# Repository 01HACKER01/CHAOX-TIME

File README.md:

# CHAOX-TIME

this is a digital alarm clock 

This is my second hardware project 
I wanted to build it all by myself alone but i dont know how to code so i used AI to make the code 
for now i have used but i will learn code asap and then make it by myself 

## BOM

| Part | Qty | Approx. USD | Link |
| -------------------------------------- | -- | ------------ | -------------------------------------------------------------------------------------------------------------------------------------------------------------- |
| Seeed XIAO ESP32-C3 | 1 | $6 | [Seeed](https://www.seeedstudio.com/Seeed-Studio-XIAO-ESP32C3-Pre-Soldered-p-6331.html) |
| 2.8" ILI9341 240×320 **8-pin SPI TFT** | 1 | $4–8 | [Alibaba – 8-pin version](https://german.alibaba.com/product-detail/2-8-Inch-240x320-SPI-Interface-1600692821834.html) |
| MCP23017-E/SP DIP-28 | 1 | ~$1.69 | [Mouser](https://www.mouser.co.uk/en/ProductDetail/Microchip-Technology/MCP23017-E-SP) |
| MAX98357A I²S amplifier module | 1 | ~$1–6 | [Alibaba MAX98357A](https://www.alibaba.com/product-detail/MAX98357A-Audio-Amplifier-Module-3006-I2S_1601639879756.html) |
| 8Ω 3W speaker | 1 | ~$1–4 | [Alibaba 8Ω 3W speakers](https://electronics.alibaba.com/buyingguides/8-ohm-3w-speaker-buying-guide) |
| 3.3V piezo buzzer | 1 | ~$0.50–1.50 | [Alibaba piezo buzzers](https://www.alibaba.com/trade/search?SearchText=3.3V+piezo+buzzer) |
| MX/Cherry-MX compatible switches | 12 | ~$3–6 | [Alibaba MX switches](https://www.alibaba.com/trade/search?SearchText=MX+mechanical+switches) |
| 1N4148 DO-35 diodes | 12 | ~$0.50–1.50 | [Alibaba 1N4148](https://www.alibaba.com/trade/search?SearchText=1N4148+DO-35) |
| 4.7kΩ ¼W THT resistors | 2 | ~$0.10–0.30 | [Alibaba 4.7k resistors](https://www.alibaba.com/trade/search?SearchText=4.7k+ohm+1%2F4W+resistor) |
| 100nF THT capacitors | 3 | ~$0.20–0.60 | [Alibaba 100nF THT capacitors](https://www.alibaba.com/trade/search?SearchText=100nF+THT+capacitor) |
| 10µF radial electrolytic capacitor | 1 | ~$0.10–0.30 | [Alibaba 10µF capacitors](https://www.alibaba.com/trade/search?SearchText=10uF+radial+electrolytic+capacitor) |
| 1×8 2.54mm header | 1 | ~$0.10–0.30 | [Alibaba 1×8 header](https://www.alibaba.com/trade/search?SearchText=1x8+2.54mm+pin+header) |
| 1×7 2.54mm header | 1 | ~$0.10–0.30 | [Alibaba 1×7 header](https://www.alibaba.com/trade/search?SearchText=1x7+2.54mm+pin+header) |
| 1×2 2.54mm header | 1 | ~$0.05–0.15 | [Alibaba 1×2 header](https://www.alibaba.com/trade/search?SearchText=1x2+2.54mm+pin+header) |
| M3×5×4 heat-set inserts | 8 | ~$1–3 | [Alibaba M3 heat-set inserts](https://www.alibaba.com/trade/search?SearchText=M3+heat+set+inserts+5x4) |
| M3×8 screws | 4 | ~$0.30–1 | [Alibaba M3×8 screws](https://www.alibaba.com/trade/search?SearchText=M3x8+screws) |
| M3×16 screws | 4 | ~$0.40–1 | [Alibaba M3×16 screws](https://www.alibaba.com/trade/search?SearchText=M3x16+screws) |
| USB-A → USB-C cable | 1 | ~$2–4 | [Alibaba USB-C cable](https://www.alibaba.com/trade/search?SearchText=USB+A+to+USB+C+cable) |
| 5V USB power adapter | 1 | ~$3–6 | [Alibaba 5V adapter](https://www.alibaba.com/trade/search?SearchText=5V+USB+power+adapter) |

### 💰 Estimated total

**Parts: About $25–50 USD**

**Estimated shipping: ~$20 USD**

**Total including shipping: About $45–70 USD**, depending heavily on the seller, quantity and shipping.

#Features 

the current verdion has some less features than what i assumed when i started this project cause i forgot i had to code it myself but i dont know how to code so rn it has some less features but i m learning c++ so that i can add all the features i thought of when i started this project 

so now the features it has rn:
- shows the current time 
- it can fetch the time and date from internet using wifi
- it can set only 1 alarm //for now
- it beeps when alarm goes off
- we can stop the alam by 1 button

i have added the hardware in the PCB for future updates 

#Hardware

The main controller is the seeed xiao esp32 c3 board which controlls the whole clock 
itt has 12 switches so that we can change any setting we want 

the pcb contains:

- Seeed XIAO ESP32-C3
- 2.8" ILI9341 SPI TFT
- MCP23017-E/SP GPIO expander
- 12 MX/Cherry-MX compatible switches
- 12 × 1N4148 diodes
- 3.3V piezo buzzer
- MAX98357A I2S audio connection
- I2C pull-up resistors
- Decoupling capacitors
- M3 mounting holes

# Controls

The keypad is arranged as a 3×4 matrix.

The current firmware uses:

- UP - increase the selected value
- DOWN - decrease the selected value
- OK - enter/confirm
- Other keys are available for future functions

To set the alarm:

1. press the OK key from the main clock screen
2. use UP/DOWN to set the alarm hour
3. press OK
4. use UP/DOWN to set the alarm minute
5. press OK again to save and enable the alarm

When the alarm starts, pressing any key stops it

- u all can change the settings and everything by making ur own firmware

# Power

CHAOX-TIME is powered from a 5V USB power adapter.

#Assemble

pcb assembly is quite easy solder eerything on its place and upload he code then screw the pcb to the case and screw the case together 
Done..

# Future Plans

I want to add more features to CHAOX-TIME over time.

Some of the things I want to add are:

- Adhan audio
- Speaker support
- Prayer times
- Multiple alarms
- Countdown timer
- Better menus
- More keypad functions
- Volume control
- More clock settings
- Saving settings
- Improved UI

These features are planned and are not part of the current firmware yet.

#THANK YOU 

#CHAOX-TIME

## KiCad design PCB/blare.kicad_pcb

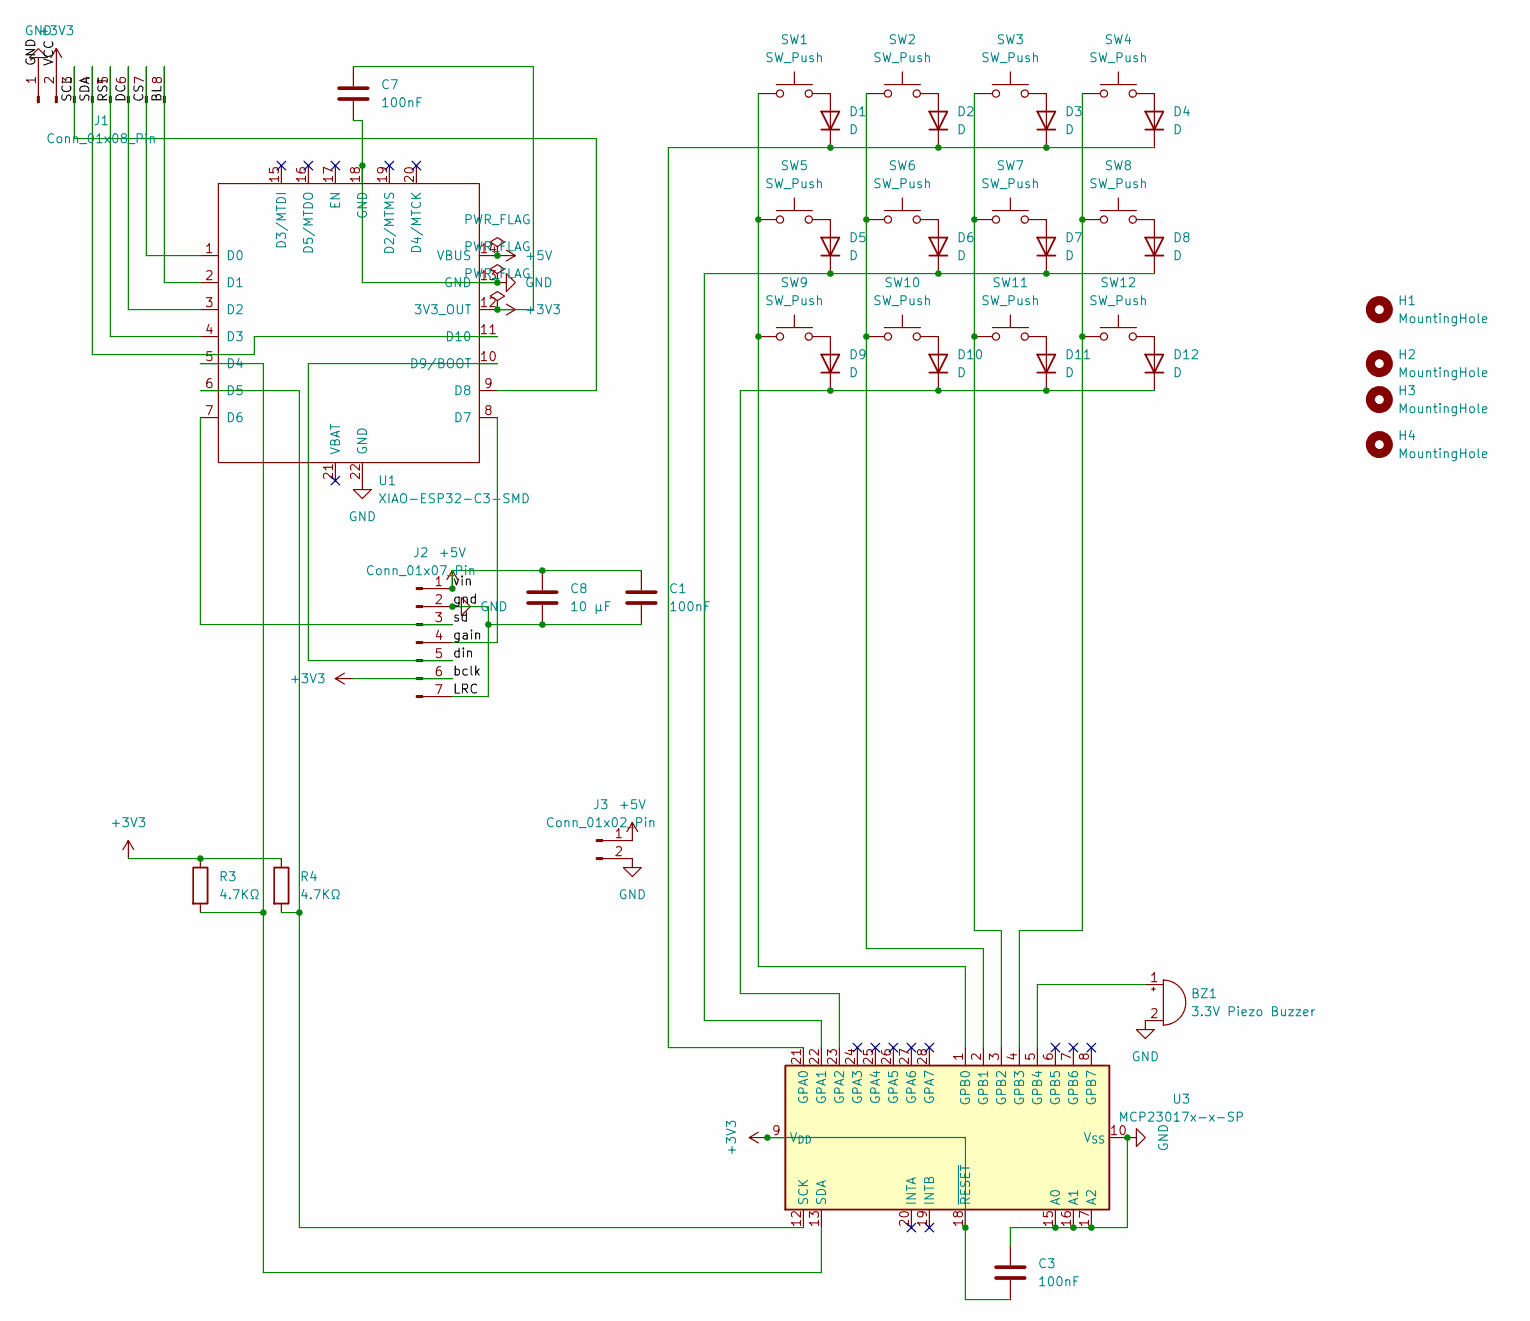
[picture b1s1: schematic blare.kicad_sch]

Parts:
BZ1: 3.3V Piezo Buzzer; Buzzer_12x9.5RM7.6
C1, C3, C7: 100nF; C_Disc_D5.0mm_W2.5mm_P2.50mm
C8: 10 µF; C_Radial_D5.0mm_H5.0mm_P2.00mm
D1, D2, D3, D4, D5, D6, D7, D8, D9, D10, D11, D12: D; D_DO-35_SOD27_P10.16mm_Horizontal
H1, H2, H3, H4: MountingHole; MountingHole_3.2mm_M3
J1: Conn_01x08_Pin; PinHeader_1x08_P2.54mm_Vertical
J2: Conn_01x07_Pin; PinHeader_1x07_P2.54mm_Vertical
J3: Conn_01x02_Pin; PinHeader_1x02_P2.54mm_Vertical
R3, R4: 4.7KΩ; R_Axial_DIN0207_L6.3mm_D2.5mm_P10.16mm_Horizontal
SW1, SW2, SW3, SW4, SW5, SW6, SW7, SW8, SW9, SW10, SW11, SW12: SW_Push; SW_Cherry_MX_1.00u_PCB
U1: XIAO-ESP32-C3-SMD; XIAO-ESP32-C3-DIP
U3: MCP23017x-x-SP; DIP-28_W7.62mm

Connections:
+3V3: C3.2, C7.1, J1.2, J2.6, R3.1, R4.1, U1.12 (3V3_OUT), U3.9 (V_{DD}), U3.18 (~RESET)
+5V: C1.1, C8.1, J2.1, J3.1, U1.14 (VBUS)
/BL: J1.8, U1.2 (D1)
/CS: J1.7, U1.1 (D0)
/DC: J1.6, U1.3 (D2)
/RST: J1.5, U1.4 (D3)
/SCL: J1.3, U1.9 (D8)
/SDA: J1.4, U1.11 (D10)
/din: J2.5, U1.10 (D9/BOOT)
/gain: J2.4, U1.8 (D7)
/sd: J2.3, U1.7 (D6)
GND: BZ1.2 (-), C1.2, C3.1, C7.2, C8.2, J1.1, J2.2, J2.7, J3.2, U1.13 (GND), U1.18 (GND), U1.22 (GND), U3.10 (V_{SS}), U3.15 (A0), U3.16 (A1), U3.17 (A2)
unnamed: BZ1.1 (+), U3.5 (GPB4)
unnamed: D1.2 (A), SW1.2
unnamed: D1.1 (K), D2.1 (K), D3.1 (K), D4.1 (K), U3.21 (GPA0)
unnamed: D2.2 (A), SW2.2
unnamed: D3.2 (A), SW3.2
unnamed: D4.2 (A), SW4.2
unnamed: D5.2 (A), SW5.2
unnamed: D5.1 (K), D6.1 (K), D7.1 (K), D8.1 (K), U3.22 (GPA1)
unnamed: D6.2 (A), SW6.2
unnamed: D7.2 (A), SW7.2
unnamed: D8.2 (A), SW8.2
unnamed: D9.2 (A), SW9.2
unnamed: D10.2 (A), SW10.2
unnamed: D9.1 (K), D10.1 (K), D11.1 (K), D12.1 (K), U3.23 (GPA2)
unnamed: D11.2 (A), SW11.2
unnamed: D12.2 (A), SW12.2
unnamed: R3.2, U1.5 (D4), U3.13 (SDA)
unnamed: R4.2, U1.6 (D5), U3.12 (SCK)
unnamed: SW1.1, SW5.1, SW9.1, U3.1 (GPB0)
unnamed: SW2.1, SW6.1, SW10.1, U3.2 (GPB1)
unnamed: SW3.1, SW7.1, SW11.1, U3.3 (GPB2)
unnamed: SW4.1, SW8.1, SW12.1, U3.4 (GPB3)

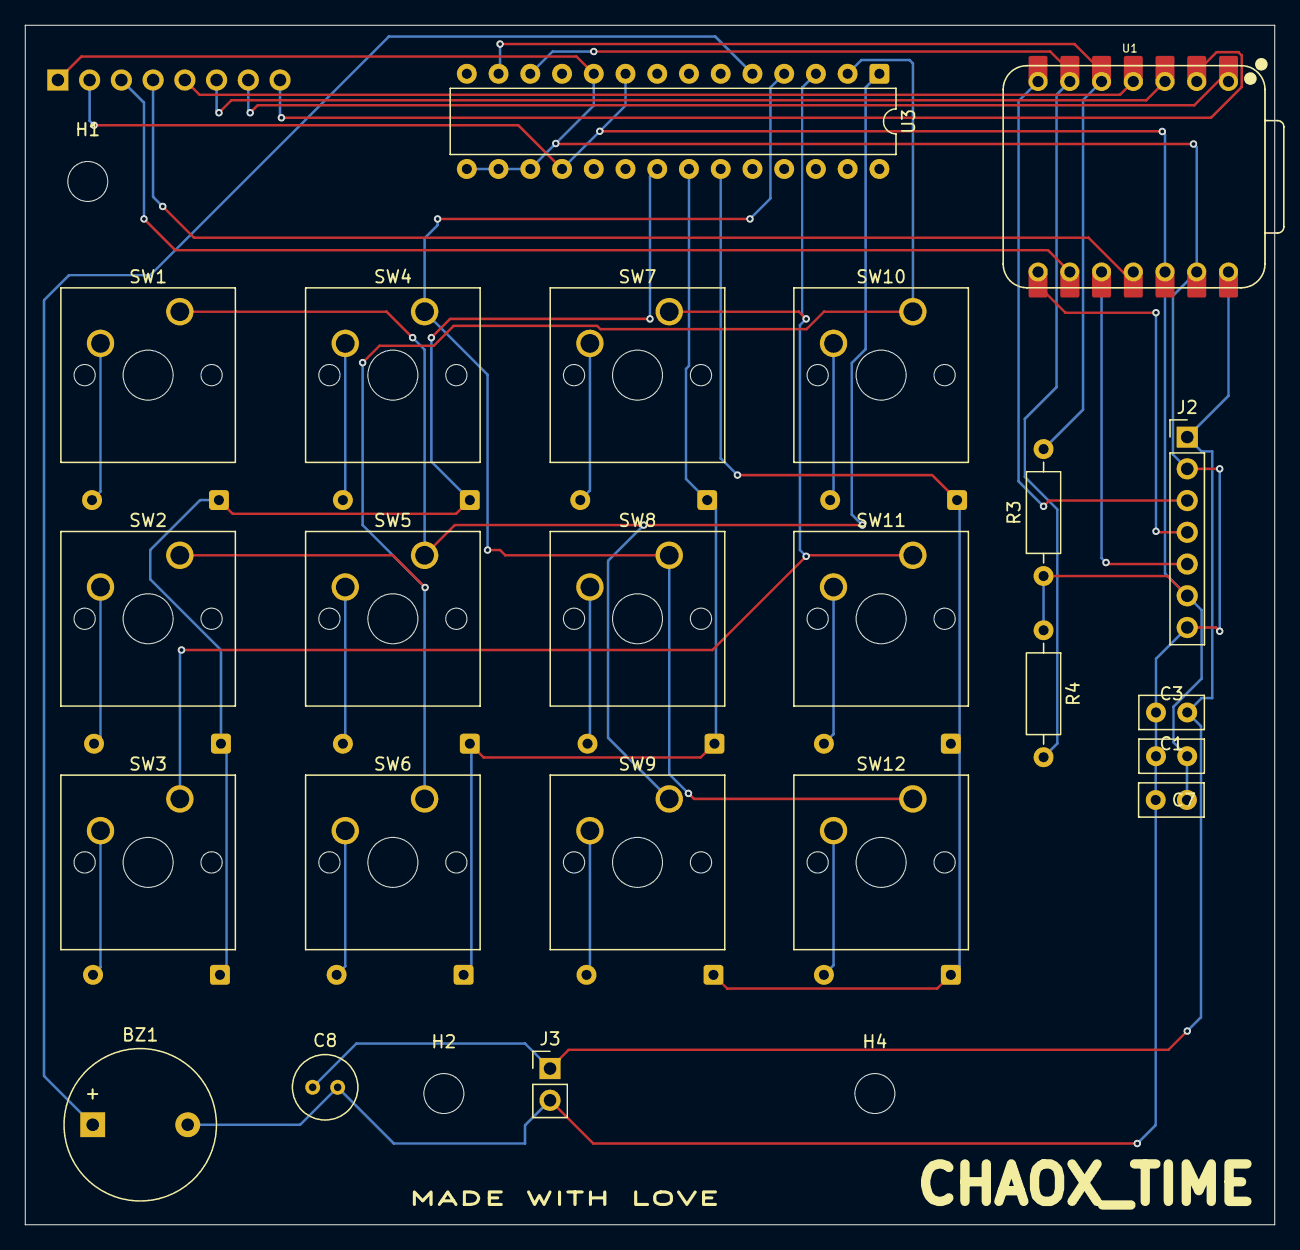
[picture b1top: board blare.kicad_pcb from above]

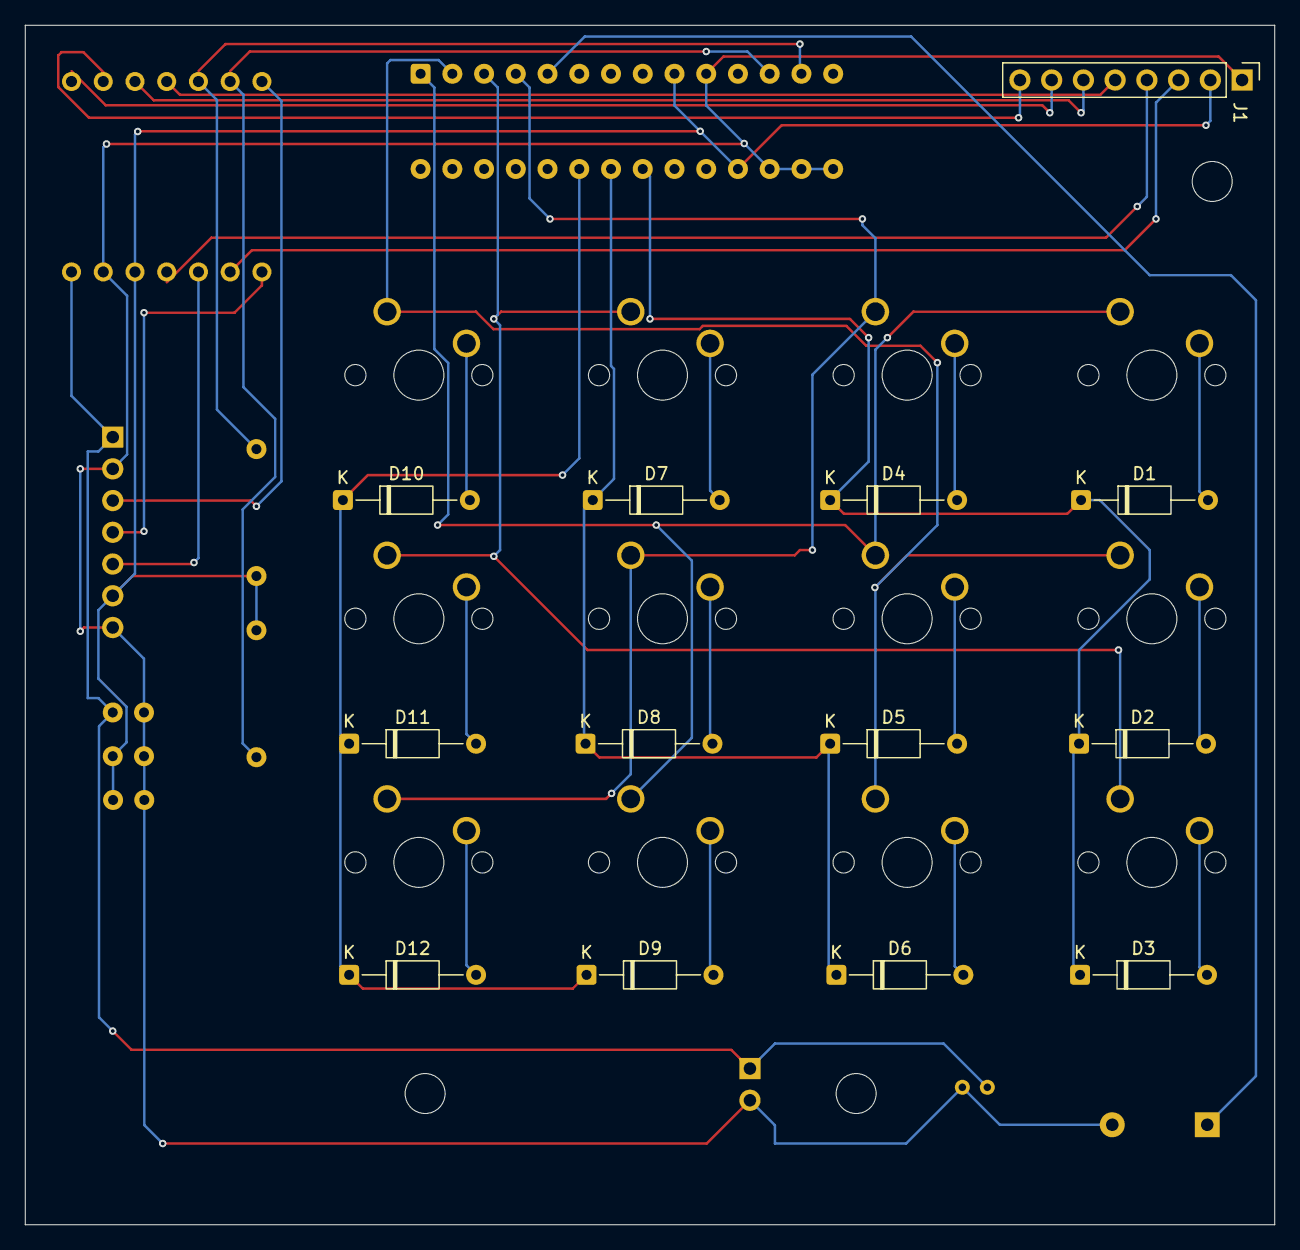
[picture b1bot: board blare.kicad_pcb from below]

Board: 2 copper layers, 100.0 x 96.0 mm, 39 parts (13 on the bottom side), 34 nets.
